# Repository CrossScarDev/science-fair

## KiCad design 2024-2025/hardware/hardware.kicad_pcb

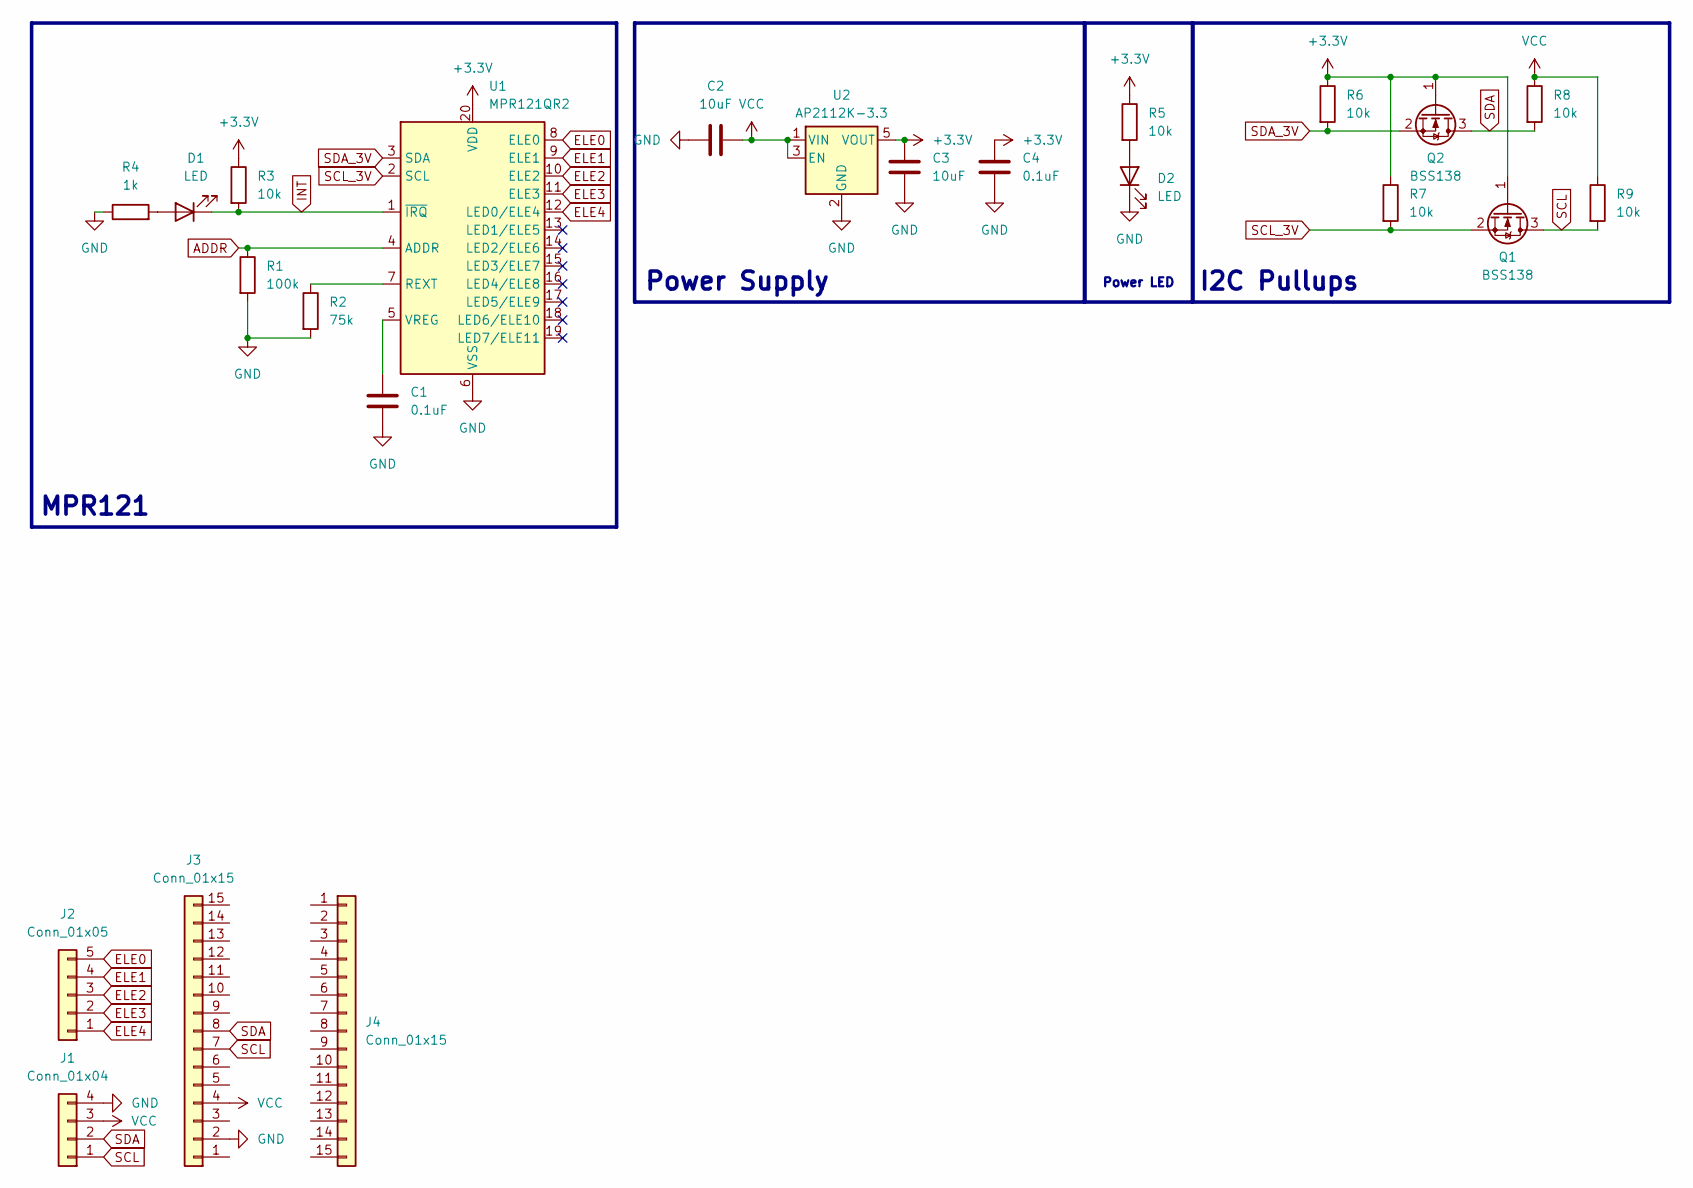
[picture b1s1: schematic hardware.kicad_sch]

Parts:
C1, C4: 0.1uF; C_0805_2012Metric
C2, C3: 10uF; C_1210_3225Metric
D1, D2: LED; LED_1206_3216Metric
J1: Conn_01x04; PinSocket_1x04_P2.54mm_Vertical
J2: Conn_01x05; PinSocket_1x05_P2.54mm_Vertical
J3, J4: Conn_01x15; PinSocket_1x15_P2.54mm_Vertical
Q1, Q2: BSS138; SOT-23
R1: 100k; R_1206_3216Metric
R2: 75k; R_1206_3216Metric
R3, R5, R6, R7, R8, R9: 10k; R_1206_3216Metric
R4: 1k; R_1206_3216Metric
U1: MPR121QR2; UQFN-20_3x3mm_P0.4mm
U2: AP2112K-3.3; SOT-23-5

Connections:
+3.3V: C3.2, C4.2, Q1.1 (G), Q2.1 (G), R3.1, R5.1, R6.1, R7.1, U1.20 (VDD), U2.5 (VOUT)
ADDR: R1.1, U1.4 (ADDR)
ELE0: J2.5, U1.8 (ELE0)
ELE1: J2.4, U1.9 (ELE1)
ELE2: J2.3, U1.10 (ELE2)
ELE3: J2.2, U1.11 (ELE3)
ELE4: J2.1, U1.12 (LED0/ELE4)
GND: C1.2, C2.1, C3.1, C4.1, D2.1 (K), J1.4, J3.2, R1.2, R2.2, R4.1, U1.6 (VSS), U2.2 (GND)
INT: D1.1 (K), R3.2, U1.1 (~IRQ)
unnamed: D1.2 (A), R4.2
unnamed: D2.2 (A), R5.2
unnamed: R2.1, U1.7 (REXT)
unnamed: C1.1, U1.5 (VREG)
SCL: J1.1, J3.7, Q1.3 (D), R9.2
SCL_3V: Q1.2 (S), R7.2, U1.2 (SCL)
SDA: J1.2, J3.8, Q2.3 (D), R8.2
SDA_3V: Q2.2 (S), R6.2, U1.3 (SDA)
VCC: C2.2, J1.3, J3.4, R8.1, R9.1, U2.1 (VIN), U2.3 (EN)

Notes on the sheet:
Power Supply
MPR121
I2C Pullups
Power LED

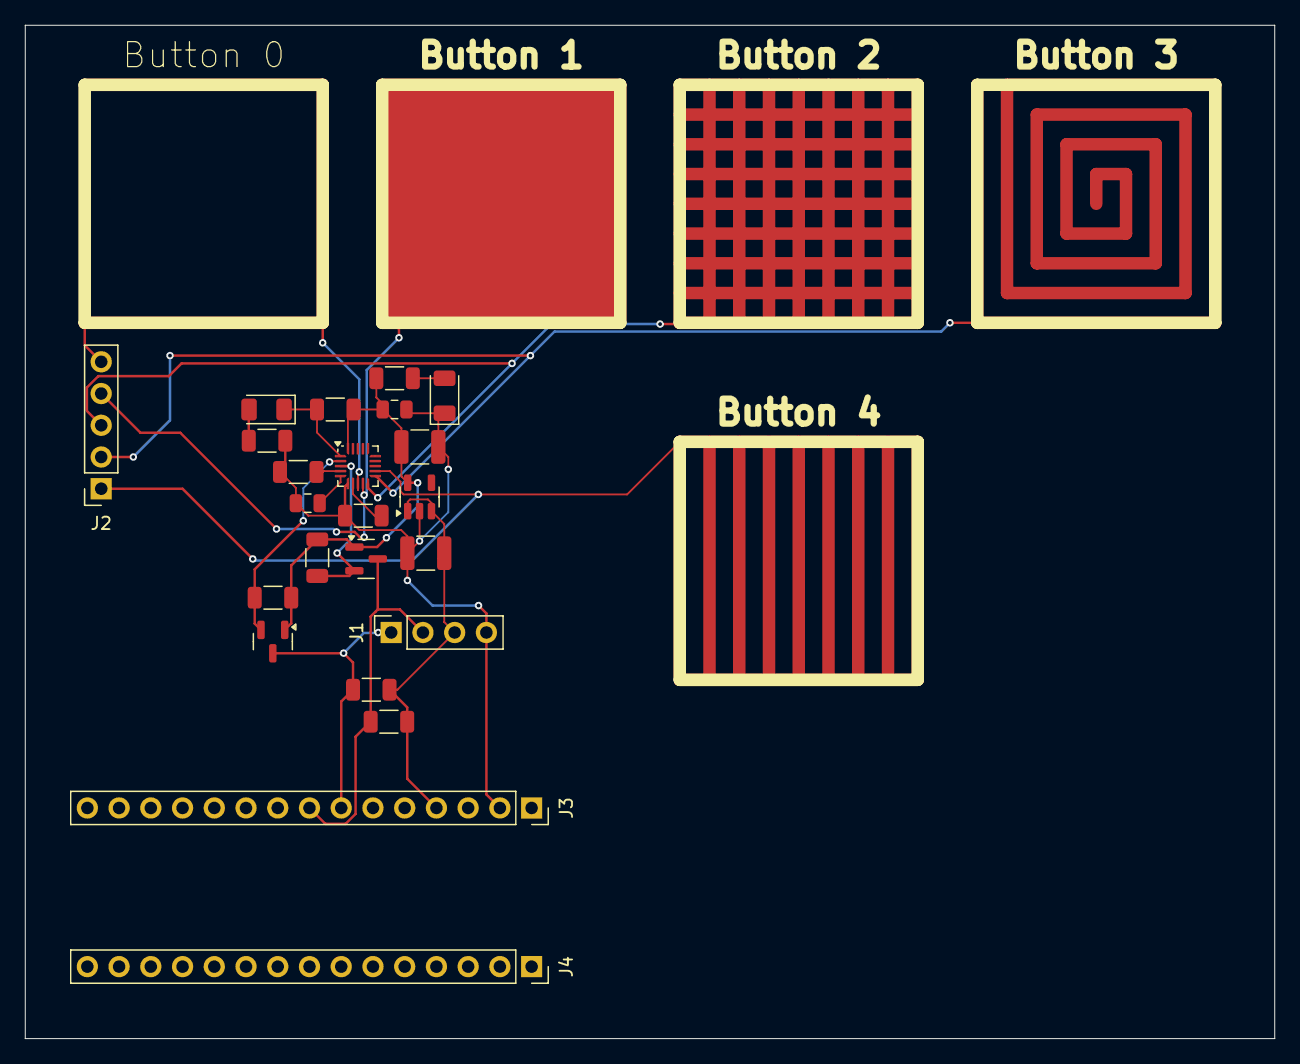
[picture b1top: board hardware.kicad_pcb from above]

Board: 2 copper layers, 100.0 x 81.1 mm, 23 parts (0 on the bottom side), 18 nets.

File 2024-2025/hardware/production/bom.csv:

Designator,Footprint,Quantity,Value,LCSC Part #
"C1, C4",0805,2,0.1uF,
"C2, C3",1210,2,10uF,
"D1, D2",1206,2,LED,
J1,PinSocket_1x04_P2.54mm_Vertical,1,Conn_01x04,
J2,PinSocket_1x05_P2.54mm_Vertical,1,Conn_01x05,
"J3, J4",PinSocket_1x15_P2.54mm_Vertical,2,Conn_01x15,
"Q1, Q2",SOT-23,2,BSS138,
R1,1206,1,100k,
R2,1206,1,75k,
"R3, R5, R6, R7, R8, R9",1206,6,10k,
R4,1206,1,1k,
U1,UQFN-20_3x3mm_P0.4mm,1,MPR121QR2,
U2,SOT-23-5,1,AP2112K-3.3,

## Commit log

2024-11-01 Init
2024-11-09 Forgot to commit this
2024-12-20 Update December 19
2024-12-20 Create KiCad SVGs
